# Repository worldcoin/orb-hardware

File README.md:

hokomsanho@gmail.com

# Worldcoin Hardware
pnpm i @worldcoin/minikit-js
คำสั่งหลากหลายลายเซ็น
Summary Submissions

ลายเซ็น
/signature

คำสั่งลายเซ็น
/recaptcha

Bot.run
As we work towards decentralization, we are incrementally open sourcing the Orb. The goal is to provide transparency and, eventually, the ability to verify our claims. Ultimately, we plan to decentralize everything involving the Orb, enabling others to develop, manufacture, and operate similar devices to issue Proof-of-Personhood credentials in a privacy-preserving manner. 

We're excited to share the engineering files of the Orb with you! For more details on how it works in detail check out [our blogpost](https://worldcoin.org/blog/engineering/opening-orb-look-inside-worldcoin-biometric-imaging-device).

If you see any issues with the design, we encourage you to create an issue to help improve future versions. 

## High-level Goals

The goal of the hardware team at Tools for Humanity is to provide products that on a high level meet the following requirements:

* Validate humanness & create a unique code to verify uniqueness in a privacy-preserving manner, as seamlessly as possible
* Ready for mobile and outdoor use (think camera equipment)
* Continuous mobile use throughout the day without significant downtime
* Enable detection of internal attacks (physical manipulation of the device) and external fraud attempts (presentation attacks) by using additional sensors that are not needed for the calculation of the unique code
* Unique visual appearance

## Hardware Products

Our initial hardware product release consists of: 

* The Orb: our core imaging device
* A custom exchangeable battery for the Orb

We will expand the scope of this repository as new products mature. We expect privacy-preserving Proof-of-Personhood to become a lasting primitive for the internet.

## Directory Structure

    ├── Orb
    │   ├── Electronics
    │   ├── Mechanics
    |   └── BOM
    |
    ├── Battery
    |   ├── Electronics
    │   ├── Mechanics
    |   └── BOM

## What's not included

### Tamper detection system not disclosed 

For obvious reasons, these files do not include the PCBs and sensors related to the Orb's tamper detection system. 

### Components pending licenses for disclosure

When designing our product, we have utilized certain proprietary information (IP) that we have not yet received confirmation from the vendor to share, or that cannot be shared as part of our open-source efforts. This includes CAD models of certain electronic boards and IP related to the electrical interface between the Jetson and the heat camera. As a result, we are currently unable to publish the bridge board that connects the main board and the front unit.

## License

Copyright 2020-2023 The Worldcoin Foundation.

You may use this package under the Worldcoin Responsible Use License, version 1.0, or at your option, any later version. See the file [COPYING](COPYING.md) for more details, and [LICENSE](LICENSE.md) for the terms of the Worldcoin Responsible Use License, version 1.0.

The Worldcoin Responsible Use License seeks a balance between fostering transparency and decentralization while preventing capture (inspired by Uniswaps [BSL](https://uniswapfoundation.mirror.xyz/lr8hUW5FFYWmvsm9ZmO6bLdLAaAx5EAnFEbJG_OTd8g) and Electric Coin Co.’s [BOSL](https://electriccoin.co/blog/introducing-tgppl-a-radically-new-type-of-open-source-license/)) and reducing the risk that Worldcoin technology could be used in harmful ways. Under the license, within about two years of publication the Worldcoin Foundation will - consistent with its governance protocols and practices at the time - review and decide whether to remove the use restrictions specified in Section II.1 of the license. Further, no more than two years after that review date, those restrictions will be lifted. As this is an unfamiliar license you may have questions or feedback. Any proposals for improvements, objections or alternative approaches are welcome.

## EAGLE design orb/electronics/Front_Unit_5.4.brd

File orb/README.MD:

## Overview
The orb consists of five modules that group our used components: 
* **Optics**: Passive optical parts (e.g., mirrors and lenses)
* **Cooling**: Passive cooling components (e.g., heat pipes)
* **Chassis**: Parts that form the internal structure
* **Outer shell**: Parts associated with the outer shell
* **Electronics**: PCBAs and other active electronic modules

If you look at our engineering data, you might find a difference between the renders of our device and the actual design. The reason is that the first design that we've put into manufacturing optimizes for precisely that. Ensure a fast time to market with an MVP and work on the final design after you have something that is manufacturable. 

## Required Tools
**Electronics**: The first release will only be EAGLE files. Later releases might be Altium. There are free viewers available for both. 

**Mechanics**: As we're releasing STP-Files, most standard CAD software should be able to open our models. If there are issues, please let us know.

## Mechanics

You can download the .stp-files [here](mechanics/download.sh).

Preview STP-File:

## Electronics
Block diagram electronics: 

Preview Mainboard:

Preview Frontunit:

## Bill of material structure
Part of our release is a drilled-down bill of material listing all the parts used in our device. 

The columns in that file are: 
* **Level**: Due to multiple assemblies in our device, we have a nested BOM. The level column tells you how deep this component is nested. E.g. *TLA, PEARL ORB, EVT* is the top-level assembly and because of that level 0, the *Gimbal Inner Axis* is for example level 4 (*TLA, PEARL ORB, EVT* -> *Optics Module* -> *OCS Front Frame* -> *Gimbal Unit*)
* **Item number**: Running number within the Assembly / Sub-Assembly
* **Partnumber**: Our internal part-number
* **Manufacturer P/N**: The part-number / unique name that our supplier uses as a part reference
* **Quantity**: Quantity of the part in the given assembly context

Please note that some parts have multiple entries in our BOM as each line lists the component in a different assembly context. 

## Directory Structure

    ├── Electronics         # Board and schematics
    ├── Mechanics           # STP-Files
    └── BOM                 # Bill of material   

## License

Copyright 2020-2023 The Worldcoin Foundation.

You may use this package under the Worldcoin Responsible Use License, version 1.0, or at your option, any later version. See the file [COPYING](../COPYING.md) for more details, and [LICENSE](../LICENSE.md) for the terms of the Worldcoin Responsible Use License, version 1.0.

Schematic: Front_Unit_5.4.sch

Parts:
C1, C2, C4, C12, C13, C14, C16, C20, C21, C22, C25, C27, C28, C30, C32, C33, C42, C43: 4u7 50V; C1210
C3, C5, C6, C7, C8, C9, C24, C26, C38: 1u 25V; C0805
C10: 27p 50V; C0603
C11: C-EU-C0603; C0603; VOLTAGE 50.0 V
C15: 100p 50V; C0603
C17, C18, C19, C23, C34, C37, C39, C40, C41, C44, C48, C49, C50, C51, C52, C53, C57, C59: 100n 50V; C0603
C45, C46, C47, C60, C78: 22u 10V; C0805
C54: n.m.; C1206; VOLTAGE 6V3
C55, C56: 22u 16V; C1206
C58: 4u7 16V; C0805
C61, C100, C102, C104, C106, C108, C110, C112, C114, C116, C118, C120, C122, C124, C126, C128, C130, C132, C134, C136, C138, C140, C142, C144, C146, C148, C150, C152, C154, C156, C158, C162, C164, C166, C168, C170, C172, C174, C176, C178, C180, C182, C184, C186, C188, C190, C192, C194, C196, C198, C200, C202, C204, C206, C208, C210, C212, C214, C216, C218, C220, C222, C224, C226, C228, C230, C232, C234, C236, C238, C240, C242, C244, C246, C248, C250, C252, C254, C256, C258, C260, C262, C264, C266, C270, C272, C280, C282, C284, C286, C288, C290, C292, C294, C296, C298, C300, C302, C304, C306, C308, C310, C312, C314, C316, C318, C320, C322, C324, C326, C328, C330, C332: 1u 25V; C0603
C101, C103, C105, C107, C109, C111, C113, C115, C117, C119, C121, C123, C125, C127, C129, C131, C133, C135, C137, C139, C141, C143, C145, C147, C149, C151, C153, C155, C157, C159, C165, C167, C169, C171, C173, C175, C177, C179, C181, C183, C185, C187, C189, C191, C193, C195, C197, C199, C201, C203, C205, C207, C209, C211, C213, C215, C217, C219, C221, C223, C225, C227, C229, C231, C233, C235, C237, C239, C241, C243, C245, C247, C249, C251, C253, C255, C257, C259, C261, C263, C265, C281, C283, C285, C287, C289, C291, C293, C295, C297, C299, C301, C303, C305, C307, C309, C311, C313, C315, C317, C319, C321, C323, C325, C327, C329, C331: C-EU-C0603; C0603; VOLTAGE 25.0 V
D1: 150060RS75000; WL-SMCW_0603_WE
D2: 150060GS75000; WL-SMCW_0603_WE
D100, D101, D102, D103, D104, D105, D106, D107, D108, D109, D110, D111, D112: LZ1-00R302; LZ1_SMALL_LEDENGIN
D200, D201, D202, D203, D204, D205, D206, D207, D208, D209, D210, D211, D212, D213, D214, D215, D250, D251, D252, D253, D254, D255, D256, D257, D258, D259, D260, D261, D262, D263, D264, D265: SST-10-IRD-B50-T850; B50_LUMINUS
D300, D301, D302, D303, D304, D305, D306, D307, D308, D309, D310, D311, D312, D313, D314, D315, D350, D351, D352, D353, D354, D355, D356, D357, D358, D359, D360, D361, D362, D363, D364, D365: SST-10-IRD-B50-S940; B50_LUMINUS
IC1, IC2, IC8, IC10, IC13: UCC27517DBV; DBV0005A_TI
IC3, IC4, IC5: LM393BIDSG; DSG0008A_WSON_TI_NO_VIA
IC7: VL53L1CBV0FY/1; VL53L1X_STM
IC9: SN74LVC112ADGV; TVSOP-16_TI
IC12, IC14, IC16, IC17, IC18, IC19, IC20: 824001; SOT23-6L_WE
IC15: TMP1075DGK; S-PDSO-G8_DGK_VSSOP_TI
IC24: TMP112NAIDRL; DRL0006A_TI
IC25: BU27030NUC; WSON008X2120_ROHM
IC31: TLV71328PDBV; R-PDSO-G5_DBV_TI
IC100, IC101, IC102, IC103, IC104, IC105, IC106, IC107, IC108, IC109, IC110, IC111, IC112, IC113, IC114, IC115, IC116, IC117, IC118, IC119, IC120, IC121, IC122, IC123, IC124, IC125, IC126, IC127, IC128, IC129, IC130, IC131, IC132, IC133, IC134, IC135, IC136, IC137, IC138, IC139, IC140, IC141, IC142, IC143, IC144, IC145, IC146, IC147, IC148, IC149, IC150, IC151, IC152, IC153, IC154, IC155, IC156, IC157, IC158, IC159, IC160, IC161, IC162, IC163, IC164, IC165, IC166, IC167, IC168, IC169, IC170, IC171, IC172, IC173, IC174, IC175, IC176, IC177, IC178, IC179, IC180, IC181, IC182, IC183, IC184, IC185, IC186, IC187, IC188, IC189, IC190, IC191, IC192, IC193, IC194, IC195, IC196, IC197, IC198, IC199, IC200, IC201, IC202, IC203, IC204, IC205, IC206, IC207, IC208, IC209, IC210, IC211, IC212, IC213, IC214, IC215, IC216, IC217, IC218, IC219, IC220, IC221, IC222, IC223, IC224, IC225, IC226, IC227, IC228, IC229, IC230, IC231, IC232, IC233, IC234, IC235, IC236, IC237, IC238, IC239, IC240, IC241, IC242, IC243, IC244, IC245, IC246, IC247, IC248, IC249, IC250, IC251, IC252, IC253, IC254, IC255, IC256, IC257, IC258, IC259, IC260, IC261, IC262, IC263, IC264, IC265, IC266, IC267, IC268, IC269, IC270, IC271, IC272, IC273, IC274, IC275, IC276, IC277, IC278, IC279, IC280, IC281, IC282, IC283, IC284, IC285, IC286, IC287, IC288, IC289, IC290, IC291, IC292, IC293, IC294, IC295, IC296, IC297, IC298, IC299, IC300, IC301, IC302, IC303, IC304, IC305, IC306, IC307, IC308, IC309, IC310, IC311, IC312, IC313, IC314, IC315, IC316, IC317, IC318, IC319, IC320, IC321, IC322, IC323, IC324, IC325, IC326, IC327, IC328, IC329, IC330, IC331, IC332: SK6805-EC15; SK6805-EC_IPIXEL
L9: 74279269; FERRIT_0603_WIDE_BAND_WUERTH
L11, L14: 742792097; FERRIT_0805_WUERTH
PS1, PS2, PS3, PS4, PS5, PS6: PASSERMARKE
R1, R9, R16, R19, R26, R27, R28, R38, R44, R47, R49, R72, R76, R78, R79: 0R; R0603
R2, R31, R40, R67: 10k; R0603
R3, R4, R5, R6, R10, R11, R12, R13, R60, R64: 56k; R0603
R7, R83, R84: 15R 0W75; R1210
R8, R15, R20, R22, R25, R29, R34, R35, R43, R46, R52, R57, R66, R69, R73, R75: 3R9 0W75; R1210
R17: 91k; R0603
R18: 27k; R0603
R21, R23, R24, R30, R32, R33, R37, R39, R54, R55, R56, R59, R80, R81, R82: 27R; R0603
R62: 1k1; R0603
R70, R71: R-EU-R0603; R0603
R87: 100R; R0603
SW1: ATE-1C-V; ATE-1C_DIPTRONICS
T2, T3, T6, T7, T10: PMV30ENEA; SOT-23_NXP
T8: NX7002AK; SOT-23_NXP
TP1: GND; TESTPAD_ROUND_1.5MM
TP2: +PVCC; TESTPAD_ROUND_1.5MM
TP3, TP4, TP5, TP6, TP7, TP8, TP9, TP10, TP11, TP12, TP14, TP15, TP16, TP17, TP18, TP19, TP20, TP21, TP22, TP23: TESTPOINT_ROUND_1.5MM; TESTPAD_ROUND_1.5MM
TP13: SAFETY_SHDN_RST; TESTPAD_ROUND_1.5MM
X1, X2: MEC6-120-02-L-DV-A; MEC6-120-02
X3: DF37NC-30DS-0.4V
X4: 687112182122; 687112182122_WUERTH
X5: AXE530127; AXE530127_PANASONIC

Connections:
!SAFETY_SHDN: C15.2, IC9.15 (!CLR), R24.2, R31.1, TP11.TP
$N200: IC325.3 (DOUT), IC326.1 (DIN)
$N201: IC327.3 (DOUT), IC328.1 (DIN)
$N202: IC329.3 (DOUT), IC330.1 (DIN)
$N203: IC331.3 (DOUT), IC332.1 (DIN)
+1V2: C46.1, X1.20, X3.27
+1V8: C37.1, C44.1, C45.1, C49.1, IC12.5 (VBUS), IC16.5 (VBUS), IC18.5 (VBUS), R16.2, X1.18, X3.28
+2V8: C50.1, IC19.5 (VBUS), X1.16
+2V8_LDO: C47.1, L14.1, X3.21
+3V3: C11.1, C15.1, C39.1, C51.1, D1.A, D2.A, IC14.5 (VBUS), IC20.5 (VBUS), L9.1, R17.2, R19.1, R26.2, R27.2, R28.2, R31.2, R40.2, R60.2, R64.2, R72.1, R76.2, R79.2, TP3.TP, X1.14
+3V6: C54.1, C55.1, C56.1, L11.2, X1.22, X5.1, X5.2, X5.3, X5.4, X5.6, X5.8
+5V: C48.1, C100.1, C101.1, C102.1, C103.1, C104.1, C105.1, C106.1, C107.1, C108.1, C109.1, C110.1, C111.1, C112.1, C113.1, C114.1, C115.1, C116.1, C117.1, C118.1, C119.1, C120.1, C121.1, C122.1, C123.1, C124.1, C125.1, C126.1, C127.1, C128.1, C129.1, C130.1, C131.1, C132.1, C133.1, C134.1, C135.1, C136.1, C137.1, C138.1, C139.1, C140.1, C141.1, C142.1, C143.1, C144.1, C145.1, C146.1, C147.1, C148.1, C149.1, C150.1, C151.1, C152.1, C153.1, C154.1, C155.1, C156.1, C157.1, C158.1, C159.1, C162.1, C164.1, C165.1, C166.1, C167.1, C168.1, C169.1, C170.1, C171.1, C172.1, C173.1, C174.1, C175.1, C176.1, C177.1, C178.1, C179.1, C180.1, C181.1, C182.1, C183.1, C184.1, C185.1, C186.1, C187.1, C188.1, C189.1, C190.1, C191.1, C192.1, C193.1, C194.1, C195.1, C196.1, C197.1, C198.1, C199.1, C200.1, C201.1, C202.1, C203.1, C204.1, C205.1, C206.1, C207.1, C208.1, C209.1, C210.1, C211.1, C212.1, C213.1, C214.1, C215.1, C216.1, C217.1, C218.1, C219.1, C220.1, C221.1, C222.1, C223.1, C224.1, C225.1, C226.1, C227.1, C228.1, C229.1, C230.1, C231.1, C232.1, C233.1, C234.1, C235.1, C236.1, C237.1, C238.1, C239.1, C240.1, C241.1, C242.1, C243.1, C244.1, C245.1, C246.1, C247.1, C248.1, C249.1, C250.1, C251.1, C252.1, C253.1, C254.1, C255.1, C256.1, C257.1, C258.1, C259.1, C260.1, C261.1, C262.1, C263.1, C264.1, C265.1, C266.1, C270.1, C272.1, C280.1, C281.1, C282.1, C283.1, C284.1, C285.1, C286.1, C287.1, C288.1, C289.1, C290.1, C291.1, C292.1, C293.1, C294.1, C295.1, C296.1, C297.1, C298.1, C299.1, C300.1, C301.1, C302.1, C303.1, C304.1, C305.1, C306.1, C307.1, C308.1, C309.1, C310.1, C311.1, C312.1, C313.1, C314.1, C315.1, C316.1, C317.1, C318.1, C319.1, C320.1, C321.1, C322.1, C323.1, C324.1, C325.1, C326.1, C327.1, C328.1, C329.1, C330.1, C331.1, C332.1, IC17.5 (VBUS), IC100.2 (VDD), IC101.2 (VDD), IC102.2 (VDD), IC103.2 (VDD), IC104.2 (VDD), IC105.2 (VDD), IC106.2 (VDD), IC107.2 (VDD), IC108.2 (VDD), IC109.2 (VDD), IC110.2 (VDD), IC111.2 (VDD), IC112.2 (VDD), IC113.2 (VDD), IC114.2 (VDD), IC115.2 (VDD), IC116.2 (VDD), IC117.2 (VDD), IC118.2 (VDD), IC119.2 (VDD), IC120.2 (VDD), IC121.2 (VDD), IC122.2 (VDD), IC123.2 (VDD), IC124.2 (VDD), IC125.2 (VDD), IC126.2 (VDD), IC127.2 (VDD), IC128.2 (VDD), IC129.2 (VDD), IC130.2 (VDD), IC131.2 (VDD), IC132.2 (VDD), IC133.2 (VDD), IC134.2 (VDD), IC135.2 (VDD), IC136.2 (VDD), IC137.2 (VDD), IC138.2 (VDD), IC139.2 (VDD), IC140.2 (VDD), IC141.2 (VDD), IC142.2 (VDD), IC143.2 (VDD), IC144.2 (VDD), IC145.2 (VDD), IC146.2 (VDD), IC147.2 (VDD), IC148.2 (VDD), IC149.2 (VDD), IC150.2 (VDD), IC151.2 (VDD), IC152.2 (VDD), IC153.2 (VDD), IC154.2 (VDD), IC155.2 (VDD), IC156.2 (VDD), IC157.2 (VDD), IC158.2 (VDD), IC159.2 (VDD), IC160.2 (VDD), IC161.2 (VDD), IC162.2 (VDD), IC163.2 (VDD), IC164.2 (VDD), IC165.2 (VDD), IC166.2 (VDD), IC167.2 (VDD), IC168.2 (VDD), IC169.2 (VDD), IC170.2 (VDD), IC171.2 (VDD), IC172.2 (VDD), IC173.2 (VDD), IC174.2 (VDD), IC175.2 (VDD), IC176.2 (VDD), IC177.2 (VDD), IC178.2 (VDD), IC179.2 (VDD), IC180.2 (VDD), IC181.2 (VDD), IC182.2 (VDD), IC183.2 (VDD), IC184.2 (VDD), IC185.2 (VDD), IC186.2 (VDD), IC187.2 (VDD), IC188.2 (VDD), IC189.2 (VDD), IC190.2 (VDD), IC191.2 (VDD), IC192.2 (VDD), IC193.2 (VDD), IC194.2 (VDD), IC195.2 (VDD), IC196.2 (VDD), IC197.2 (VDD), IC198.2 (VDD), IC199.2 (VDD), IC200.2 (VDD), IC201.2 (VDD), IC202.2 (VDD), IC203.2 (VDD), IC204.2 (VDD), IC205.2 (VDD), IC206.2 (VDD), IC207.2 (VDD), IC208.2 (VDD), IC209.2 (VDD), IC210.2 (VDD), IC211.2 (VDD), IC212.2 (VDD), IC213.2 (VDD), IC214.2 (VDD), IC215.2 (VDD), IC216.2 (VDD), IC217.2 (VDD), IC218.2 (VDD), IC219.2 (VDD), IC220.2 (VDD), IC221.2 (VDD), IC222.2 (VDD), IC223.2 (VDD), IC224.2 (VDD), IC225.2 (VDD), IC226.2 (VDD), IC227.2 (VDD), IC228.2 (VDD), IC229.2 (VDD), IC230.2 (VDD), IC231.2 (VDD), IC232.2 (VDD), IC233.2 (VDD), IC234.2 (VDD), IC235.2 (VDD), IC236.2 (VDD), IC237.2 (VDD), IC238.2 (VDD), IC239.2 (VDD), IC240.2 (VDD), IC241.2 (VDD), IC242.2 (VDD), IC243.2 (VDD), IC244.2 (VDD), IC245.2 (VDD), IC246.2 (VDD), IC247.2 (VDD), IC248.2 (VDD), IC249.2 (VDD), IC250.2 (VDD), IC251.2 (VDD), IC252.2 (VDD), IC253.2 (VDD), IC254.2 (VDD), IC255.2 (VDD), IC256.2 (VDD), IC257.2 (VDD), IC258.2 (VDD), IC259.2 (VDD), IC260.2 (VDD), IC261.2 (VDD), IC262.2 (VDD), IC263.2 (VDD), IC264.2 (VDD), IC265.2 (VDD), IC266.2 (VDD), IC267.2 (VDD), IC268.2 (VDD), IC269.2 (VDD), IC270.2 (VDD), IC271.2 (VDD), IC272.2 (VDD), IC273.2 (VDD), IC274.2 (VDD), IC275.2 (VDD), IC276.2 (VDD), IC277.2 (VDD), IC278.2 (VDD), IC279.2 (VDD), IC280.2 (VDD), IC281.2 (VDD), IC282.2 (VDD), IC283.2 (VDD), IC284.2 (VDD), IC285.2 (VDD), IC286.2 (VDD), IC287.2 (VDD), IC288.2 (VDD), IC289.2 (VDD), IC290.2 (VDD), IC291.2 (VDD), IC292.2 (VDD), IC293.2 (VDD), IC294.2 (VDD), IC295.2 (VDD), IC296.2 (VDD), IC297.2 (VDD), IC298.2 (VDD), IC299.2 (VDD), IC300.2 (VDD), IC301.2 (VDD), IC302.2 (VDD), IC303.2 (VDD), IC304.2 (VDD), IC305.2 (VDD), IC306.2 (VDD), IC307.2 (VDD), IC308.2 (VDD), IC309.2 (VDD), IC310.2 (VDD), IC311.2 (VDD), IC312.2 (VDD), IC313.2 (VDD), IC314.2 (VDD), IC315.2 (VDD), IC316.2 (VDD), IC317.2 (VDD), IC318.2 (VDD), IC319.2 (VDD), IC320.2 (VDD), IC321.2 (VDD), IC322.2 (VDD), IC323.2 (VDD), IC324.2 (VDD), IC325.2 (VDD)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
+PVCC: C1.1, C2.1, C4.1, C12.1, C13.1, C14.1, C16.1, C20.1, C21.1, C22.1, C25.1, C27.1, C28.1, C30.1, C32.1, C33.1, C41.1, C42.1, C43.1, R7.2, R8.2, R15.2, R20.2, R22.2, R25.2, R29.2, R34.2, R35.2, R43.2, R46.2, R52.2, R57.2, R66.2, R69.2, R73.2, R75.2, R83.2, R84.2, TP2.TP, X2.02 (2), X2.04 (4), X2.06 (6), X2.08 (8)
+VBAT: R1.1, R9.1, R38.1, R44.1, R78.1, TP4.TP, X1.30
CAM1_RGB_!PWDN_1V8: IC12.3 (I/O2), X1.08 (8), X3.26
CAM1_RGB_CLK_N: X1.05 (5), X3.5
CAM1_RGB_CLK_P: X1.03 (3), X3.4
CAM1_RGB_D0_N: X1.11, X3.8
CAM1_RGB_D0_P: X1.09 (9), X3.7
CAM1_RGB_D1_N: X1.17, X3.11
CAM1_RGB_D1_P: X1.15, X3.10
CAM1_RGB_I2C_SCL_1V8: IC12.4 (I/O3), X1.12, X3.2
CAM1_RGB_I2C_SDA_1V8: IC12.6 (I/O4), X1.10, X3.1
CAM1_RGB_MCLK_1V8: IC12.1 (I/O1), X1.04 (4), X3.24
CAM3_TOF_!PWDN!_1V8: IC18.6 (I/O4), X2.16, X5.30
CAM3_TOF_CLK_N: X2.36, X5.23
CAM3_TOF_CLK_P: X2.38, X5.21
CAM3_TOF_D0_N: X2.27, X5.17
CAM3_TOF_D0_P: X2.29, X5.15
CAM3_TOF_D1_N: X2.30, X5.29
CAM3_TOF_D1_P: X2.32, X5.27
CAM3_TOF_I2C_SCL_1V8: IC18.1 (I/O1), X2.22, X5.24
CAM3_TOF_I2C_SDA_1V8: IC18.3 (I/O2), X2.20, X5.26
CAM3_TOF_MCLK_1V8: IC18.4 (I/O3), R47.1, X2.33
COPY_SIG_1: IC101.3 (DOUT), IC102.1 (DIN)
COPY_SIG_2: IC102.3 (DOUT), IC103.1 (DIN)
FET_DRV_!EN: IC1.4 (IN-), IC2.4 (IN-), IC8.4 (IN-), IC10.4 (IN-), IC13.4 (IN-), T8.3 (D)
FU_I2C_TEMP_SCL_3V3: IC14.4 (I/O3), R32.2, R39.2, R82.2, TP22.TP, X1.29
FU_I2C_TEMP_SDA_3V3: IC14.3 (I/O2), R30.2, R33.2, R81.2, TP23.TP, X1.31
FU_PVCC_EN_3V3: IC14.6 (I/O4), R55.2, R60.1, R62.1, T8.1 (G), TP10.TP, X1.27
FU_TAMPER_SWITCH: SW1.3 (NO), SW1.4 (NO), X1.34
GND: C1.2, C2.2, C3.2, C4.2, C5.2, C6.2, C7.2, C8.2, C9.2, C10.2, C12.2, C13.2, C14.2, C16.2, C17.2, C18.2, C19.2, C20.2, C21.2, C22.2, C23.2, C24.2, C25.2, C26.2, C27.2, C28.2, C30.2, C32.2, C33.2, C34.2, C37.2, C38.2, C39.2, C40.2, C41.2, C42.2, C43.2, C44.2, C45.2, C46.2, C47.2, C48.2, C49.2, C50.2, C51.2, C52.2, C53.2, C54.2, C55.2, C56.2, C57.2, C58.2, C59.2, C60.2, C61.2, C78.2, C100.2, C101.2, C102.2, C103.2, C104.2, C105.2, C106.2, C107.2, C108.2, C109.2, C110.2, C111.2, C112.2, C113.2, C114.2, C115.2, C116.2, C117.2, C118.2, C119.2, C120.2, C121.2, C122.2, C123.2, C124.2, C125.2, C126.2, C127.2, C128.2, C129.2, C130.2, C131.2, C132.2, C133.2, C134.2, C135.2, C136.2, C137.2, C138.2, C139.2, C140.2, C141.2, C142.2, C143.2, C144.2, C145.2, C146.2, C147.2, C148.2, C149.2, C150.2, C151.2, C152.2, C153.2, C154.2, C155.2, C156.2, C157.2, C158.2, C159.2, C162.2, C164.2, C165.2, C166.2, C167.2, C168.2, C169.2, C170.2, C171.2, C172.2, C173.2, C174.2, C175.2, C176.2, C177.2, C178.2, C179.2, C180.2, C181.2, C182.2, C183.2, C184.2, C185.2, C186.2, C187.2, C188.2, C189.2, C190.2, C191.2, C192.2, C193.2, C194.2, C195.2, C196.2, C197.2, C198.2, C199.2, C200.2, C201.2, C202.2, C203.2, C204.2, C205.2, C206.2, C207.2, C208.2, C209.2, C210.2, C211.2, C212.2, C213.2, C214.2, C215.2, C216.2, C217.2, C218.2, C219.2, C220.2, C221.2, C222.2, C223.2, C224.2, C225.2, C226.2, C227.2, C228.2, C229.2, C230.2, C231.2, C232.2, C233.2, C234.2, C235.2, C236.2, C237.2, C238.2, C239.2, C240.2, C241.2, C242.2, C243.2, C244.2, C245.2, C246.2, C247.2, C248.2, C249.2, C250.2, C251.2, C252.2, C253.2, C254.2, C255.2, C256.2, C257.2, C258.2, C259.2, C260.2, C261.2, C262.2, C263.2, C264.2, C265.2, C266.2, C270.2, C272.2, C280.2, C281.2, C282.2, C283.2, C284.2, C285.2, C286.2, C287.2, C288.2, C289.2, C290.2, C291.2, C292.2, C293.2, C294.2, C295.2, C296.2, C297.2, C298.2, C299.2, C300.2, C301.2, C302.2, C303.2, C304.2, C305.2, C306.2, C307.2, C308.2, C309.2, C310.2, C311.2, C312.2, C313.2, C314.2, C315.2, C316.2, C317.2, C318.2, C319.2, C320.2, C321.2, C322.2, C323.2, C324.2, C325.2, C326.2, C327.2, C328.2, C329.2, C330.2, C331.2, C332.2, D100.5, D101.5, D102.5, D103.5, D104.5, D105.5, D106.5, D107.5, D108.5, D109.5, D110.5, D111.5, D112.5, D200.NC, D201.NC, D202.NC, D203.NC, D204.NC, D205.NC, D206.NC, D207.NC, D208.NC, D209.NC, D210.NC, D211.NC, D212.NC, D213.NC, D214.NC, D215.NC, D250.NC, D251.NC, D252.NC, D253.NC, D254.NC, D255.NC, D256.NC, D257.NC, D258.NC, D259.NC, D260.NC, D261.NC, D262.NC, D263.NC, D264.NC, D265.NC, D300.NC, D301.NC, D302.NC, D303.NC, D304.NC, D305.NC, D306.NC, D307.NC, D308.NC, D309.NC, D310.NC, D311.NC, D312.NC, D313.NC, D314.NC, D315.NC, D350.NC, D351.NC, D352.NC, D353.NC, D354.NC, D355.NC, D356.NC, D357.NC, D358.NC, D359.NC, D360.NC, D361.NC, D362.NC, D363.NC, D364.NC, D365.NC, IC1.2 (GND), IC2.2 (GND), IC3.4 (GND), IC3.PAD (GND), IC4.4 (GND), IC4.6 (-IN), IC4.PAD (GND), IC5.4 (GND), IC5.6 (-IN), IC5.PAD (GND), IC7.2 (AVSSVCSEL), IC7.3 (GND), IC7.4 (GND), IC7.6 (GND), IC7.12 (GND), IC8.2 (GND), IC9.1 (CLK), IC9.2 (K), IC9.3 (J), IC9.8 (GND), IC9.10 (!PRE), IC9.11 (J), IC9.12 (K), IC9.13 (CLK), IC9.14 (!CLR), IC10.2 (GND), IC12.2 (GND), IC13.2 (GND), IC14.2 (GND), IC15.4 (GND), IC15.5 (A2), IC15.6 (A1), IC15.7 (A0), IC16.2 (GND), IC17.2 (GND), IC18.2 (GND), IC19.2 (GND), IC20.2 (GND), IC24.2 (GND), IC24.4 (ADD0), IC25.3 (GND), IC25.PAD (GND), IC31.2 (GND), IC31.4 (GND), IC100.4 (VSS), IC101.4 (VSS), IC102.4 (VSS), IC103.4 (VSS), IC104.4 (VSS), IC105.4 (VSS), IC106.4 (VSS), IC107.4 (VSS), IC108.4 (VSS), IC109.4 (VSS), IC110.4 (VSS), IC111.4 (VSS), IC112.4 (VSS), IC113.4 (VSS), IC114.4 (VSS), IC115.4 (VSS), IC116.4 (VSS), IC117.4 (VSS), IC118.4 (VSS), IC119.4 (VSS), IC120.4 (VSS), IC121.4 (VSS), IC122.4 (VSS), IC123.4 (VSS), IC124.4 (VSS), IC125.4 (VSS), IC126.4 (VSS), IC127.4 (VSS), IC128.4 (VSS), IC129.4 (VSS), IC130.4 (VSS), IC131.4 (VSS), IC132.4 (VSS), IC133.4 (VSS), IC134.4 (VSS), IC135.4 (VSS), IC136.4 (VSS), IC137.4 (VSS), IC138.4 (VSS), IC139.4 (VSS), IC140.4 (VSS), IC141.4 (VSS), IC142.4 (VSS), IC143.4 (VSS), IC144.4 (VSS), IC145.4 (VSS), IC146.4 (VSS), IC147.4 (VSS), IC148.4 (VSS), IC149.4 (VSS), IC150.4 (VSS)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
HEAT_CAM_ARESET_N_2V8: IC20.4 (I/O3), X2.23, X4.5
HEAT_CAM_FPA_EN_2V8: IC19.6 (I/O4), X2.13, X4.10
HEAT_CAM_MISO_2V8: IC19.1 (I/O1), R87.2, X2.19
HEAT_CAM_MOSI_2V8: IC19.3 (I/O2), X2.17, X4.8
HEAT_CAM_SCLK_2V8: IC19.4 (I/O3), X2.15, X4.9
HEAT_CAM_SCT_NSS_2V8: IC20.6 (I/O4), X2.21, X4.6
unnamed: D306.A, D307.C
unnamed: D350.C, D357.A
unnamed: D304.A, D305.C
unnamed: D314.A, D315.C
unnamed: D313.A, D314.C
unnamed: D312.A, D313.C
unnamed: C57.1, C58.1, IC7.1 (AVDDVCSEL), IC7.11 (AVDD), R2.2, R19.2
unnamed: D311.A, D312.C
unnamed: D303.A, D304.C
unnamed: D302.A, D303.C
unnamed: D301.A, D302.C
unnamed: D300.A, D301.C
unnamed: IC8.5 (OUT), R54.1, TP5.TP
unnamed: R54.2, T6.1 (G)
unnamed: D352.A, D353.C
unnamed: D351.A, D352.C
unnamed: D350.A, D351.C
unnamed: D360.A, D361.C
unnamed: D359.A, D360.C
unnamed: IC1.5 (OUT), R21.1
unnamed: R21.2, T2.1 (G), TP15.TP
unnamed: D358.A, D359.C
unnamed: C24.1, IC8.1 (VDD), R38.2
unnamed: D252.A, D253.C
unnamed: D251.A, D252.C
unnamed: D250.A, D251.C
unnamed: D310.A, D311.C
unnamed: D309.A, D310.C
unnamed: D308.A, D309.C
unnamed: D202.A, D203.C
unnamed: D201.A, D202.C
unnamed: D200.A, D201.C
unnamed: C3.1, IC1.1 (VDD), R1.2
unnamed: D356.C, D358.C, T6.3 (D)
unnamed: D355.A, R43.1, R46.1
unnamed: D365.A, R66.1, R69.1
unnamed: D363.A, D364.C
unnamed: D356.A, D357.C
unnamed: D354.A, D355.C
unnamed: D364.A, D365.C
unnamed: C60.1, IC31.1 (IN), IC31.3 (EN), L11.1
unnamed: D362.A, D363.C
unnamed: D306.C, D308.C, T2.3 (D)
unnamed: IC10.5 (OUT), R59.1
unnamed: R59.2, T7.1 (G), TP16.TP
unnamed: C26.1, IC10.1 (VDD), R44.2
unnamed: IC2.5 (OUT), R23.1
unnamed: R87.1, X4.7
unnamed: D300.C, D307.A
unnamed: D353.A, D354.C
unnamed: C61.1, IC31.5 (OUT), L14.2
unnamed: D361.A, D362.C
unnamed: IC7.5 (XSHUT), R2.1
unnamed: D257.A, D258.C
unnamed: D255.A, D256.C
unnamed: D254.A, D255.C
unnamed: C6.1, IC3.2 (-IN), R10.2
unnamed: D206.A, D215.C
unnamed: D205.A, D206.C
unnamed: D204.A, D205.C
unnamed: D253.A, D254.C
unnamed: D203.A, D204.C
unnamed: C34.1, IC9.16 (VCC), R76.1
unnamed: IC9.6 (!Q), R56.1
unnamed: IC9.5 (Q), R55.1
unnamed: C23.1, IC9.4 (!PRE), R37.2, R40.1
unnamed: D1.C, R62.2
unnamed: C7.1, IC3.6 (-IN), R11.2
unnamed: C17.1, IC3.8 (VCC), R26.1
unnamed: D2.C, R67.2
unnamed: D305.A, R8.1, R15.1
unnamed: D315.A, R25.1, R29.1
unnamed: D215.A, R20.1, R22.1
unnamed: D265.A, R52.1, R57.1
unnamed: R23.2, T3.1 (G), TP6.TP
unnamed: IC7.10 (SCL), R32.1
unnamed: IC15.1 (SDA), IC24.6 (SDA), R81.1
unnamed: C40.1, IC15.8 (VCC), IC24.5 (V+), R79.1
unnamed: D210.A, D211.C
unnamed: D209.A, D210.C
unnamed: IC15.2 (SCL), IC24.1 (SCL), R82.1
unnamed: C5.1, IC2.1 (VDD), R9.2
unnamed: IC13.5 (OUT), R80.1, TP18.TP
unnamed: R80.2, T10.1 (G)
unnamed: C38.1, IC13.1 (VDD), R78.2
unnamed: D105.1 (C), D105.4 (C), T10.3 (D)
unnamed: D104.1 (C), D104.4 (C), D105.2 (A), D105.3 (A)
unnamed: D103.1 (C), D103.4 (C), D104.2 (A), D104.3 (A)
unnamed: D102.1 (C), D102.4 (C), D103.2 (A), D103.3 (A)
unnamed: D101.1 (C), D101.4 (C), D102.2 (A), D102.3 (A)
unnamed: D100.1 (C), D100.4 (C), D101.2 (A), D101.3 (A)
unnamed: D100.2 (A), D100.3 (A), D112.1 (C), D112.4 (C)
unnamed: D111.1 (C), D111.4 (C), D112.2 (A), D112.3 (A)
unnamed: D110.1 (C), D110.4 (C), D111.2 (A), D111.3 (A)
unnamed: D109.1 (C), D109.4 (C), D110.2 (A), D110.3 (A)
unnamed: D108.1 (C), D108.4 (C), D109.2 (A), D109.3 (A)
unnamed: D107.1 (C), D107.4 (C), D108.2 (A), D108.3 (A)
unnamed: D106.1 (C), D106.4 (C), D107.2 (A), D107.3 (A)
unnamed: D106.2 (A), D106.3 (A), R7.1, R83.1, R84.1
unnamed: D208.A, D209.C
unnamed: C8.1, IC4.2 (-IN), R12.2
unnamed: C9.1, IC5.2 (-IN), R13.2
unnamed: D214.A, R34.1, R35.1
unnamed: C18.1, IC4.8 (VCC), R27.1
unnamed: D207.A, D208.C
unnamed: D213.A, D214.C
unnamed: C11.2, IC3.3 (+IN), IC3.5 (+IN), IC4.3 (+IN), IC4.5 (+IN), IC5.3 (+IN), IC5.5 (+IN), R17.1, R18.2
unnamed: C19.1, IC5.8 (VCC), R28.1
unnamed: IC3.1 (OUT), IC3.7 (OUT), IC4.1 (OUT), IC5.1 (OUT), IC5.7 (OUT), R24.1
unnamed: D212.A, D213.C
unnamed: D211.A, D212.C
unnamed: D200.C, D207.C, T3.3 (D)
unnamed: D260.A, D261.C
unnamed: D259.A, D260.C
unnamed: D258.A, D259.C
unnamed: D264.A, R73.1, R75.1
unnamed: D256.A, D265.C
unnamed: D263.A, D264.C
unnamed: D262.A, D263.C
unnamed: D261.A, D262.C
unnamed: D250.C, D257.C, T7.3 (D)
unnamed: IC324.3 (DOUT), IC325.1 (DIN)
unnamed: IC326.3 (DOUT), IC327.1 (DIN)
unnamed: IC7.9 (SDA), R30.1
unnamed: C78.1, R16.1, X5.10, X5.12, X5.14
unnamed: R47.2, X5.11
unnamed: IC25.5 (SCL), R39.1
unnamed: IC25.6 (SDA), R33.1
unnamed: C59.1, IC25.2 (VCC), R71.2, R72.2
unnamed: IC25.1 (TEST), R49.2, R71.1
unnamed: IC25.4 (DNC1), R70.2
unnamed: IC330.3 (DOUT), IC331.1 (DIN)
PVCC_DISABLE: R56.2, R64.1, R67.1, TP12.TP
RBG_DOUT_END: IC323.3 (DOUT), TP9.TP
RGB_DOUT_0: IC100.3 (DOUT), IC101.1 (DIN)
RGB_DOUT_3: IC103.3 (DOUT), IC104.1 (DIN)
RGB_DOUT_4: IC104.3 (DOUT), IC105.1 (DIN)
RGB_DOUT_5: IC105.3 (DOUT), IC106.1 (DIN)
RGB_DOUT_6: IC106.3 (DOUT), IC107.1 (DIN)
RGB_DOUT_7: IC107.3 (DOUT), IC108.1 (DIN)
RGB_DOUT_8: IC108.3 (DOUT), IC109.1 (DIN)
RGB_DOUT_9: IC109.3 (DOUT), IC110.1 (DIN)
RGB_DOUT_10: IC110.3 (DOUT), IC111.1 (DIN)
RGB_DOUT_11: IC111.3 (DOUT), IC112.1 (DIN)
RGB_DOUT_12: IC112.3 (DOUT), IC113.1 (DIN)
RGB_DOUT_13: IC113.3 (DOUT), IC114.1 (DIN)
RGB_DOUT_14: IC114.3 (DOUT), IC115.1 (DIN)
RGB_DOUT_15: IC115.3 (DOUT), IC116.1 (DIN)
RGB_DOUT_16: IC116.3 (DOUT), IC117.1 (DIN)
RGB_DOUT_17: IC117.3 (DOUT), IC118.1 (DIN)
RGB_DOUT_18: IC118.3 (DOUT), IC119.1 (DIN)
RGB_DOUT_19: IC119.3 (DOUT), IC120.1 (DIN)
RGB_DOUT_20: IC120.3 (DOUT), IC121.1 (DIN)
RGB_DOUT_21: IC121.3 (DOUT), IC122.1 (DIN)
RGB_DOUT_22: IC122.3 (DOUT), IC123.1 (DIN)
RGB_DOUT_23: IC123.3 (DOUT), IC124.1 (DIN)
RGB_DOUT_24: IC124.3 (DOUT), IC125.1 (DIN)
RGB_DOUT_25: IC125.3 (DOUT), IC126.1 (DIN)
RGB_DOUT_26: IC126.3 (DOUT), IC127.1 (DIN)
RGB_DOUT_27: IC127.3 (DOUT), IC128.1 (DIN)
RGB_DOUT_28: IC128.3 (DOUT), IC129.1 (DIN)
RGB_DOUT_29: IC129.3 (DOUT), IC130.1 (DIN)
RGB_DOUT_30: IC130.3 (DOUT), IC131.1 (DIN)
RGB_DOUT_31: IC131.3 (DOUT), IC132.1 (DIN)
RGB_DOUT_32: IC132.3 (DOUT), IC133.1 (DIN)
RGB_DOUT_33: IC133.3 (DOUT), IC134.1 (DIN)
RGB_DOUT_34: IC134.3 (DOUT), IC135.1 (DIN)
RGB_DOUT_35: IC135.3 (DOUT), IC136.1 (DIN)
RGB_DOUT_36: IC136.3 (DOUT), IC137.1 (DIN)
RGB_DOUT_37: IC137.3 (DOUT), IC138.1 (DIN)
RGB_DOUT_38: IC138.3 (DOUT), IC139.1 (DIN)
RGB_DOUT_39: IC139.3 (DOUT), IC140.1 (DIN)
RGB_DOUT_40: IC140.3 (DOUT), IC141.1 (DIN)
RGB_DOUT_41: IC141.3 (DOUT), IC142.1 (DIN)
RGB_DOUT_42: IC142.3 (DOUT), IC143.1 (DIN)
RGB_DOUT_43: IC143.3 (DOUT), IC144.1 (DIN)
RGB_DOUT_44: IC144.3 (DOUT), IC145.1 (DIN)
RGB_DOUT_45: IC145.3 (DOUT), IC146.1 (DIN)
RGB_DOUT_46: IC146.3 (DOUT), IC147.1 (DIN)
RGB_DOUT_47: IC147.3 (DOUT), IC148.1 (DIN)
RGB_DOUT_48: IC148.3 (DOUT), IC149.1 (DIN)
RGB_DOUT_49: IC149.3 (DOUT), IC150.1 (DIN)
RGB_DOUT_50: IC150.3 (DOUT), IC151.1 (DIN)
RGB_DOUT_51: IC151.3 (DOUT), IC152.1 (DIN)
RGB_DOUT_52: IC152.3 (DOUT), IC153.1 (DIN)
RGB_DOUT_53: IC153.3 (DOUT), IC154.1 (DIN)
RGB_DOUT_54: IC154.3 (DOUT), IC155.1 (DIN)
RGB_DOUT_55: IC155.3 (DOUT), IC156.1 (DIN)
RGB_DOUT_56: IC156.3 (DOUT), IC157.1 (DIN)
RGB_DOUT_57: IC157.3 (DOUT), IC158.1 (DIN)
RGB_DOUT_58: IC158.3 (DOUT), IC159.1 (DIN)
RGB_DOUT_59: IC159.3 (DOUT), IC160.1 (DIN)
RGB_DOUT_60: IC160.3 (DOUT), IC161.1 (DIN)
RGB_DOUT_61: IC161.3 (DOUT), IC162.1 (DIN)
RGB_DOUT_62: IC162.3 (DOUT), IC163.1 (DIN)
RGB_DOUT_63: IC163.3 (DOUT), IC164.1 (DIN)
RGB_DOUT_64: IC164.3 (DOUT), IC165.1 (DIN)
RGB_DOUT_65: IC165.3 (DOUT), IC166.1 (DIN)
RGB_DOUT_66: IC166.3 (DOUT), IC167.1 (DIN)
RGB_DOUT_67: IC167.3 (DOUT), IC168.1 (DIN)
RGB_DOUT_68: IC168.3 (DOUT), IC169.1 (DIN)
RGB_DOUT_69: IC169.3 (DOUT), IC170.1 (DIN)
RGB_DOUT_70: IC170.3 (DOUT), IC171.1 (DIN)
RGB_DOUT_71: IC171.3 (DOUT), IC172.1 (DIN)
RGB_DOUT_72: IC172.3 (DOUT), IC173.1 (DIN)
RGB_DOUT_73: IC173.3 (DOUT), IC174.1 (DIN)
RGB_DOUT_74: IC174.3 (DOUT), IC175.1 (DIN)
RGB_DOUT_75: IC175.3 (DOUT), IC176.1 (DIN)
RGB_DOUT_76: IC176.3 (DOUT), IC177.1 (DIN)
RGB_DOUT_77: IC177.3 (DOUT), IC178.1 (DIN)
RGB_DOUT_78: IC178.3 (DOUT), IC179.1 (DIN)
RGB_DOUT_79: IC179.3 (DOUT), IC180.1 (DIN)
RGB_DOUT_80: IC180.3 (DOUT), IC181.1 (DIN)
RGB_DOUT_81: IC181.3 (DOUT), IC182.1 (DIN)
RGB_DOUT_82: IC182.3 (DOUT), IC183.1 (DIN)
RGB_DOUT_83: IC183.3 (DOUT), IC184.1 (DIN)
RGB_DOUT_84: IC184.3 (DOUT), IC185.1 (DIN)
RGB_DOUT_85: IC185.3 (DOUT), IC186.1 (DIN)
RGB_DOUT_86: IC186.3 (DOUT), IC187.1 (DIN)
RGB_DOUT_87: IC187.3 (DOUT), IC188.1 (DIN)
RGB_DOUT_88: IC188.3 (DOUT), IC189.1 (DIN)
RGB_DOUT_89: IC189.3 (DOUT), IC190.1 (DIN)
RGB_DOUT_90: IC190.3 (DOUT), IC191.1 (DIN)
RGB_DOUT_91: IC191.3 (DOUT), IC192.1 (DIN)
RGB_DOUT_92: IC192.3 (DOUT), IC193.1 (DIN)
RGB_DOUT_93: IC193.3 (DOUT), IC194.1 (DIN)
RGB_DOUT_94: IC194.3 (DOUT), IC195.1 (DIN)
RGB_DOUT_95: IC195.3 (DOUT), IC196.1 (DIN)
RGB_DOUT_96: IC196.3 (DOUT), IC197.1 (DIN)
RGB_DOUT_97: IC197.3 (DOUT), IC198.1 (DIN)
RGB_DOUT_98: IC198.3 (DOUT), IC199.1 (DIN)
RGB_DOUT_99: IC199.3 (DOUT), IC200.1 (DIN)
RGB_DOUT_100: IC200.3 (DOUT), IC201.1 (DIN)
RGB_DOUT_101: IC201.3 (DOUT), IC202.1 (DIN)
RGB_DOUT_102: IC202.3 (DOUT), IC203.1 (DIN)
RGB_DOUT_103: IC203.3 (DOUT), IC204.1 (DIN)
RGB_DOUT_104: IC204.3 (DOUT), IC205.1 (DIN)
RGB_DOUT_105: IC205.3 (DOUT), IC206.1 (DIN)
RGB_DOUT_106: IC206.3 (DOUT), IC207.1 (DIN)
RGB_DOUT_107: IC207.3 (DOUT), IC208.1 (DIN)
RGB_DOUT_108: IC208.3 (DOUT), IC209.1 (DIN)
RGB_DOUT_109: IC209.3 (DOUT), IC210.1 (DIN)
RGB_DOUT_110: IC210.3 (DOUT), IC211.1 (DIN)
RGB_DOUT_111: IC211.3 (DOUT), IC212.1 (DIN)
RGB_DOUT_112: IC212.3 (DOUT), IC213.1 (DIN)
RGB_DOUT_113: IC213.3 (DOUT), IC214.1 (DIN)
RGB_DOUT_114: IC214.3 (DOUT), IC215.1 (DIN)
RGB_DOUT_115: IC215.3 (DOUT), IC216.1 (DIN)
RGB_DOUT_116: IC216.3 (DOUT), IC217.1 (DIN)
RGB_DOUT_117: IC217.3 (DOUT), IC218.1 (DIN)
RGB_DOUT_118: IC218.3 (DOUT), IC219.1 (DIN)
RGB_DOUT_119: IC219.3 (DOUT), IC220.1 (DIN)
RGB_DOUT_120: IC220.3 (DOUT), IC221.1 (DIN)
RGB_DOUT_121: IC221.3 (DOUT), IC222.1 (DIN)
RGB_DOUT_122: IC222.3 (DOUT), IC223.1 (DIN)
RGB_DOUT_123: IC223.3 (DOUT), IC224.1 (DIN)
RGB_DOUT_124: IC224.3 (DOUT), IC225.1 (DIN)
RGB_DOUT_125: IC225.3 (DOUT), IC226.1 (DIN)
RGB_DOUT_126: IC226.3 (DOUT), IC227.1 (DIN)
RGB_DOUT_127: IC227.3 (DOUT), IC228.1 (DIN)
RGB_DOUT_128: IC228.3 (DOUT), IC229.1 (DIN)
RGB_DOUT_129: IC229.3 (DOUT), IC230.1 (DIN)
RGB_DOUT_130: IC230.3 (DOUT), IC231.1 (DIN)
RGB_DOUT_131: IC231.3 (DOUT), IC232.1 (DIN)
RGB_DOUT_132: IC232.3 (DOUT), IC233.1 (DIN)
RGB_DOUT_133: IC233.3 (DOUT), IC234.1 (DIN)
RGB_DOUT_134: IC234.3 (DOUT), IC235.1 (DIN)
RGB_DOUT_135: IC235.3 (DOUT), IC236.1 (DIN)
RGB_DOUT_136: IC236.3 (DOUT), IC237.1 (DIN)
RGB_DOUT_137: IC237.3 (DOUT), IC238.1 (DIN)
RGB_DOUT_138: IC238.3 (DOUT), IC239.1 (DIN)
RGB_DOUT_139: IC239.3 (DOUT), IC240.1 (DIN)
RGB_DOUT_140: IC240.3 (DOUT), IC241.1 (DIN)
RGB_DOUT_141: IC241.3 (DOUT), IC242.1 (DIN)
RGB_DOUT_142: IC242.3 (DOUT), IC243.1 (DIN)
RGB_DOUT_143: IC243.3 (DOUT), IC244.1 (DIN)
RGB_DOUT_144: IC244.3 (DOUT), IC245.1 (DIN)
RGB_DOUT_145: IC245.3 (DOUT), IC246.1 (DIN)
RGB_DOUT_146: IC246.3 (DOUT), IC247.1 (DIN)
RGB_DOUT_147: IC247.3 (DOUT), IC248.1 (DIN)
RGB_DOUT_148: IC248.3 (DOUT), IC249.1 (DIN)
RGB_DOUT_149: IC249.3 (DOUT), IC250.1 (DIN)
RGB_DOUT_150: IC250.3 (DOUT), IC251.1 (DIN)
RGB_DOUT_151: IC251.3 (DOUT), IC252.1 (DIN)
RGB_DOUT_152: IC252.3 (DOUT), IC253.1 (DIN)
RGB_DOUT_153: IC253.3 (DOUT), IC254.1 (DIN)
RGB_DOUT_154: IC254.3 (DOUT), IC255.1 (DIN)
RGB_DOUT_155: IC255.3 (DOUT), IC256.1 (DIN)
RGB_DOUT_156: IC256.3 (DOUT), IC257.1 (DIN)
RGB_DOUT_157: IC257.3 (DOUT), IC258.1 (DIN)
RGB_DOUT_158: IC258.3 (DOUT), IC259.1 (DIN)
RGB_DOUT_159: IC259.3 (DOUT), IC260.1 (DIN)
RGB_DOUT_160: IC260.3 (DOUT), IC261.1 (DIN)
RGB_DOUT_161: IC261.3 (DOUT), IC262.1 (DIN)
RGB_DOUT_162: IC262.3 (DOUT), IC263.1 (DIN)
RGB_DOUT_163: IC263.3 (DOUT), IC264.1 (DIN)
RGB_DOUT_164: IC264.3 (DOUT), IC265.1 (DIN)
RGB_DOUT_165: IC265.3 (DOUT), IC266.1 (DIN)
RGB_DOUT_166: IC266.3 (DOUT), IC267.1 (DIN)
RGB_DOUT_167: IC267.3 (DOUT), IC268.1 (DIN)
RGB_DOUT_168: IC268.3 (DOUT), IC269.1 (DIN)
RGB_DOUT_169: IC269.3 (DOUT), IC270.1 (DIN)
RGB_DOUT_170: IC270.3 (DOUT), IC271.1 (DIN)
RGB_DOUT_171: IC271.3 (DOUT), IC272.1 (DIN)
RGB_DOUT_172: IC272.3 (DOUT), IC273.1 (DIN)
RGB_DOUT_173: IC273.3 (DOUT), IC274.1 (DIN)
RGB_DOUT_174: IC274.3 (DOUT), IC275.1 (DIN)
RGB_DOUT_175: IC275.3 (DOUT), IC276.1 (DIN)
RGB_DOUT_176: IC276.3 (DOUT), IC277.1 (DIN)
RGB_DOUT_177: IC277.3 (DOUT), IC278.1 (DIN)
RGB_DOUT_178: IC278.3 (DOUT), IC279.1 (DIN)
RGB_DOUT_179: IC279.3 (DOUT), IC280.1 (DIN)
RGB_DOUT_180: IC280.3 (DOUT), IC281.1 (DIN)
RGB_DOUT_181: IC281.3 (DOUT), IC282.1 (DIN)
RGB_DOUT_182: IC282.3 (DOUT), IC283.1 (DIN)
RGB_DOUT_183: IC283.3 (DOUT), IC284.1 (DIN)
RGB_DOUT_184: IC284.3 (DOUT), IC285.1 (DIN)
RGB_DOUT_185: IC285.3 (DOUT), IC286.1 (DIN)
RGB_DOUT_186: IC286.3 (DOUT), IC287.1 (DIN)
RGB_DOUT_187: IC287.3 (DOUT), IC288.1 (DIN)
RGB_DOUT_188: IC288.3 (DOUT), IC289.1 (DIN)
RGB_DOUT_189: IC289.3 (DOUT), IC290.1 (DIN)
RGB_DOUT_190: IC290.3 (DOUT), IC291.1 (DIN)
RGB_DOUT_191: IC291.3 (DOUT), IC292.1 (DIN)
RGB_DOUT_192: IC292.3 (DOUT), IC293.1 (DIN)
RGB_DOUT_193: IC293.3 (DOUT), IC294.1 (DIN)
RGB_DOUT_194: IC294.3 (DOUT), IC295.1 (DIN)
RGB_DOUT_195: IC295.3 (DOUT), IC296.1 (DIN)
RGB_DOUT_196: IC296.3 (DOUT), IC297.1 (DIN)
RGB_DOUT_197: IC297.3 (DOUT), IC298.1 (DIN)
RGB_DOUT_198: IC298.3 (DOUT), IC299.1 (DIN)
RGB_DOUT_199: IC299.3 (DOUT), IC300.1 (DIN)
RGB_DOUT_200: IC300.3 (DOUT), IC301.1 (DIN)
RGB_DOUT_201: IC301.3 (DOUT), IC302.1 (DIN)
RGB_DOUT_202: IC302.3 (DOUT), IC303.1 (DIN)
RGB_DOUT_203: IC303.3 (DOUT), IC304.1 (DIN)
RGB_DOUT_204: IC304.3 (DOUT), IC305.1 (DIN)
RGB_DOUT_205: IC305.3 (DOUT), IC306.1 (DIN)
RGB_DOUT_206: IC306.3 (DOUT), IC307.1 (DIN)
RGB_DOUT_207: IC307.3 (DOUT), IC308.1 (DIN)
RGB_DOUT_208: IC308.3 (DOUT), IC309.1 (DIN)
RGB_DOUT_209: IC309.3 (DOUT), IC310.1 (DIN)
RGB_DOUT_210: IC310.3 (DOUT), IC311.1 (DIN)
RGB_DOUT_211: IC311.3 (DOUT), IC312.1 (DIN)
RGB_DOUT_212: IC312.3 (DOUT), IC313.1 (DIN)
RGB_DOUT_213: IC313.3 (DOUT), IC314.1 (DIN)
RGB_DOUT_214: IC314.3 (DOUT), IC315.1 (DIN)
RGB_DOUT_215: IC315.3 (DOUT), IC316.1 (DIN)
RGB_DOUT_216: IC316.3 (DOUT), IC317.1 (DIN)
RGB_DOUT_217: IC317.3 (DOUT), IC318.1 (DIN)
RGB_DOUT_218: IC318.3 (DOUT), IC319.1 (DIN)
RGB_DOUT_219: IC319.3 (DOUT), IC320.1 (DIN)
RGB_DOUT_220: IC320.3 (DOUT), IC321.1 (DIN)
RGB_DOUT_221: IC321.3 (DOUT), IC322.1 (DIN)
RGB_DOUT_222: IC322.3 (DOUT), IC323.1 (DIN)
RGB_DOUT_228: IC328.3 (DOUT), IC329.1 (DIN)
RGB_DOUT_232: IC100.1 (DIN), IC332.3 (DOUT)
RGB_LED_UC->FU_5V: C10.1, IC17.4 (I/O3), IC324.1 (DIN), TP8.TP, X1.24
SAFETY_SHDN_RST: R37.1, TP13.TP
UC_CAM3_TOF_TRIGGER_TO_SENSOR_1V8: IC16.1 (I/O1), X2.26, X5.18
UC_FU_740NM_3V3: IC13.3 (IN+), IC14.1 (I/O1), TP19.TP, X1.35
UC_FU_850NM_LEFT_3V3: IC2.3 (IN+), IC17.3 (I/O2), R5.2, R12.1, TP20.TP, X1.37
UC_FU_850NM_RIGHT_3V3: IC10.3 (IN+), IC20.3 (I/O2), R6.2, R13.1, TP21.TP, X2.12
UC_FU_940NM_LEFT_3V3: IC1.3 (IN+), IC17.1 (I/O1), R3.2, R10.1, TP14.TP, X1.38
UC_FU_940NM_RIGHT_3V3: IC8.3 (IN+), IC20.1 (I/O1), R4.2, R11.1, TP17.TP, X2.14
VCC_IO: C52.1, X4.4
VIN_A: C53.1, L9.2, X4.3

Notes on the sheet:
RGB CAM + TOF CAM + Heat Cam
Changelog 2.0 - IR LEDs SFH4780S (810nm) replaced by SST-10-IRD-B50-T850 (850nm) and SST-10-IRD-B50-S940 (940nm) - Connector X10 620110131822 -> 68711214522 - CH101 (ultrasonic ToF sensor) added - Boost converter für high current pulsing added - Buck-Boost converter added - Safety shutdown circuit 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
SST-10-IRD-B50-S940: I_f,typ = 3.00V @ 0.75A = 3.35V @ 1.5A<<< = 3.80V @ 2.5A = 5.00V @ 5.0A
SST-10-IRD-B50-T850 I_f,typ = 2.75 V @ 0.1A = 3.20V @ 0.75A = 3.55V @ 1.5A ~2A <<<<< = 4.00V @ 2.5A = 5.20V @ 5.0A
IR LEDs 940 nm 1/2
Safety circuit 1/2
f_CLK = 1 ... 2560 kHz
address: 1001000b
Temperature Sensor
IR LEDs 940 nm 2/2
IR LEDs 850 nm 1/2
LZ1-00R302 I_f,typ = 2.20 V @ 1.0 A
IR LEDs 740 nm
Safety circuit 2/2
open drain outputs @ LM393B
Card edge connector
IR LEDs 850 nm 2/2
IR850_Left(16)
IR940_Left (16)
IR940_Right (16)
IR850_Right(16)
+PVCC = 31.3 V
RGB_RING (224)
RGB_UX_DOT (9)
IR940_2L (10)
IR940_2R (10)
IR940_1L (6)
IR940_1R (6)
IR850_2L (9)
IR850_2R (9)
IR850_1L (7)
IR850_1R (7)
IR740_1 (6)
IR740_2 (7)
IR740 (13) + Temp Sensor
RGB CAM
TOF CAM
Heat Cam
Connector Bridge PCB
Safety Circuit

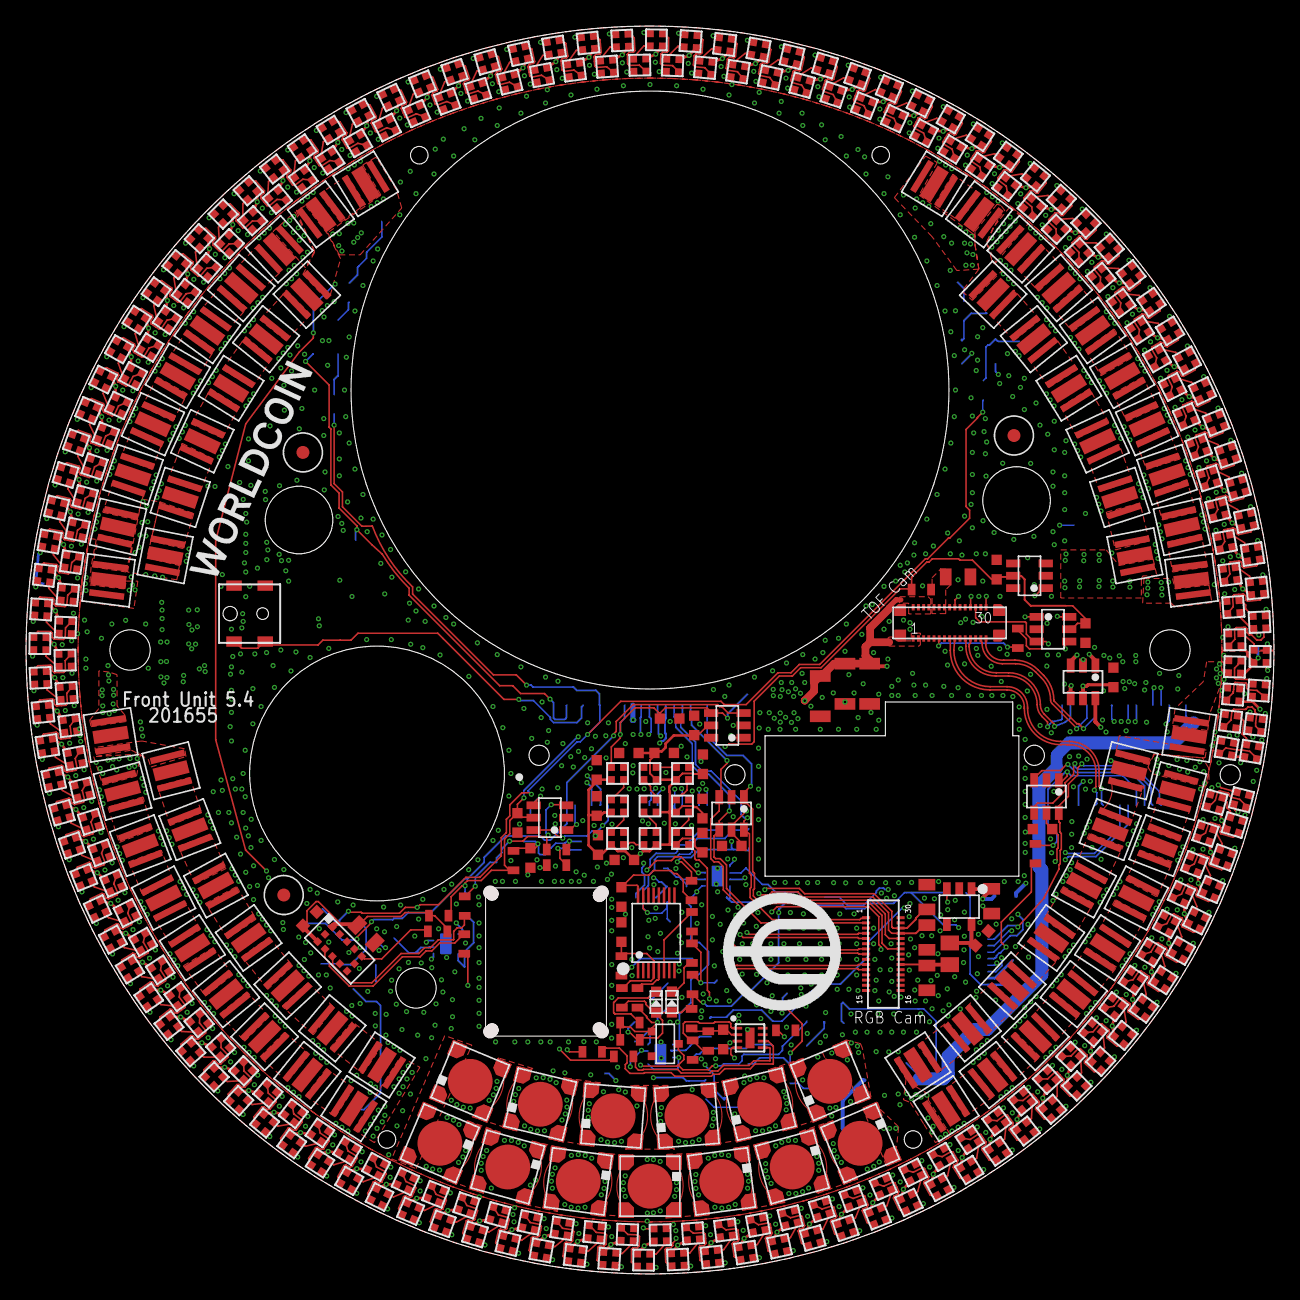
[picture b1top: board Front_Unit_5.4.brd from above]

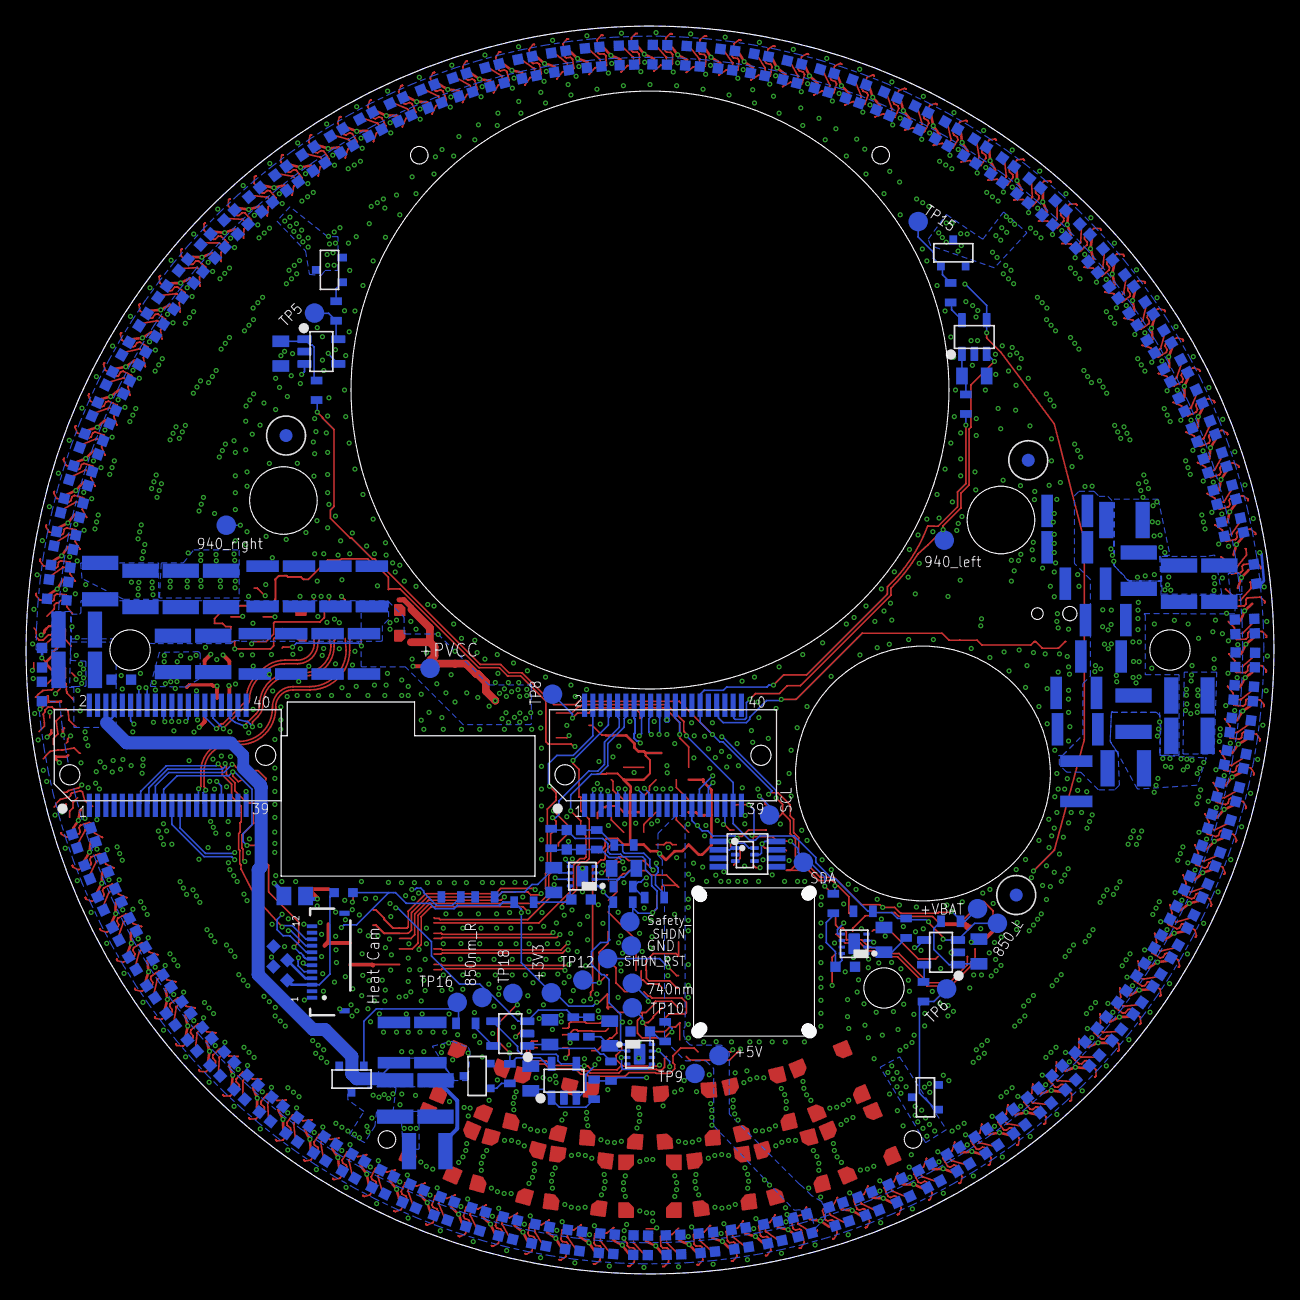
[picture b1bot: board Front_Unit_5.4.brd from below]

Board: 4 copper layers, 96.0 x 96.0 mm, 723 parts (335 on the bottom side), 415 nets.
